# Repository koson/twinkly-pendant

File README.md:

twinkly-pendant
===============

Twinkly pendant or earring, about 25mm diameter PCB with MSP430G2231 14TSSOP, 8x 0805 LEDs, and LiR2032.

The intention is to use near-visible UV LEDs (~395nm). Central area for mounting uranium glass button.

To protect against accidental discharge, unclip from metal chain and/or findings when not in use and 
store in ESD safe packaging.

Versions
--------

_PE01_

Initial prototype with SMD LEDs.

_PE02_

Second prototype with through-hole LEDs.
Buzzer circuit requires 39 mH inductor in parallel with piezo diaphragm.
3 PCBs ordered from OSHpark.

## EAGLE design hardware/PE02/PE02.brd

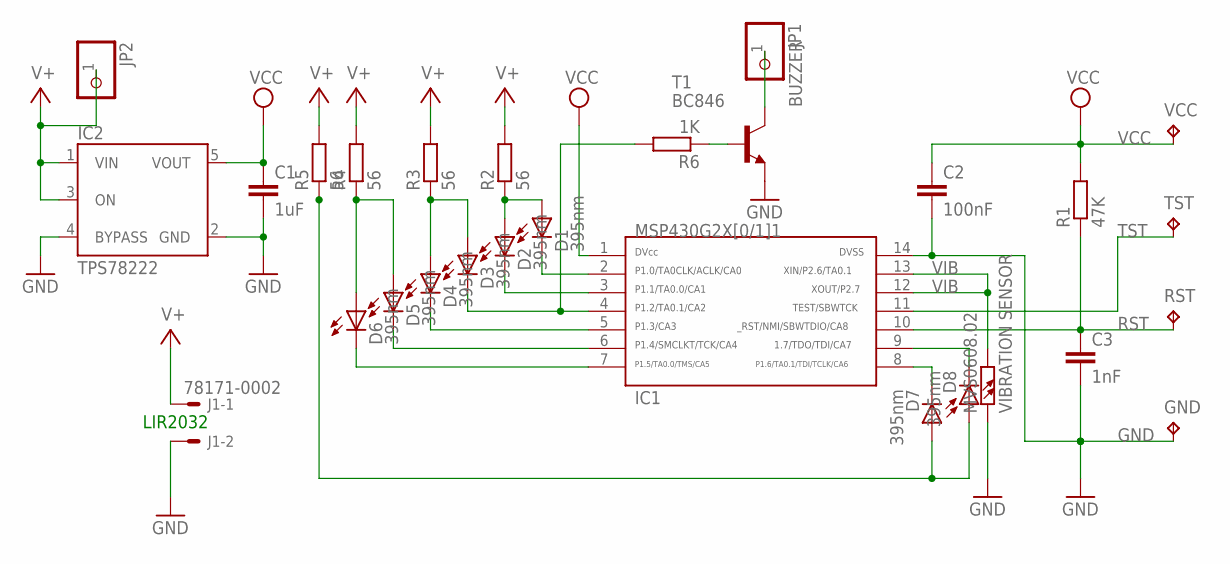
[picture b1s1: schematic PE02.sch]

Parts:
C1: 1uF; 0805
C2: 100nF; 0805
C3: 1nF; 0805
D1, D2, D3, D4, D5, D6, D7, D8: 395nm; LED-3MM
GND: TPTP10R; TP10R
IC1: MSP430G2231; PW14
IC2: TPS78222; SOT23-5
J1: 78171-0002
JP1, JP2: PINHD-1X1CB; 1X01-CLEANBIG
MVS0608.02: VIBRATION SENSOR; R1210
R1: 47K; R0603
R2, R3, R4, R5: 56; R0603
R6: 1K; R0603
RST: TPTP10R; TP10R
T1: BC846; SOT23
TST: TPTP10R; TP10R
VCC: TPTP10R; TP10R

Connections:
BUZZER: JP1.1, T1.3 (C)
GND: C1.2, C2.2, C3.2, GND.TP, IC1.14, IC2.2 (GND), IC2.4 (BYPASS), J1.2, MVS0608.02.1, T1.2 (E)
unnamed: D6.K (C), IC1.7
unnamed: D5.K (C), IC1.6
unnamed: D8.K (C), IC1.9
unnamed: D7.K (C), IC1.8
unnamed: D4.K (C), IC1.5
unnamed: D3.K (C), IC1.4, R6.2
unnamed: D1.K (C), IC1.2
unnamed: R6.1, T1.1 (B)
unnamed: D7.A, D8.A, R5.1
unnamed: D2.K (C), IC1.3
unnamed: D3.A, D4.A, R3.1
unnamed: D5.A, D6.A, R4.1
unnamed: D1.A, D2.A, R2.1
RST: C3.1, IC1.10, R1.1, RST.TP
TST: IC1.11, TST.TP
V+: IC2.1 (VIN), IC2.3 (ON), J1.1, JP2.1, R2.2, R3.2, R4.2, R5.2
VCC: C1.1, C2.1, IC1.1, IC2.5 (VOUT), R1.2, VCC.TP
VIB: IC1.12, IC1.13, MVS0608.02.2

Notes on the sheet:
LIR2032

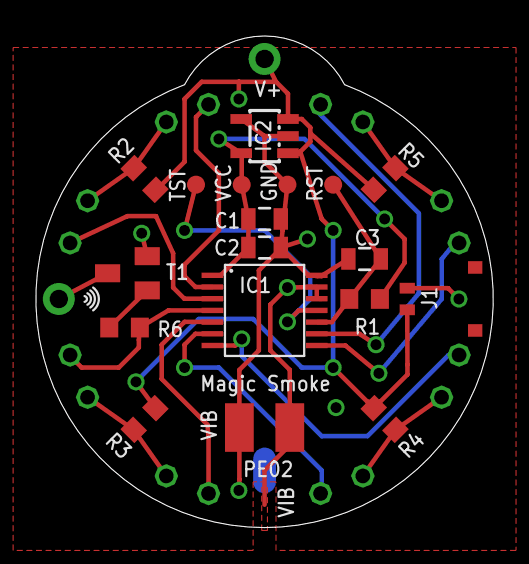
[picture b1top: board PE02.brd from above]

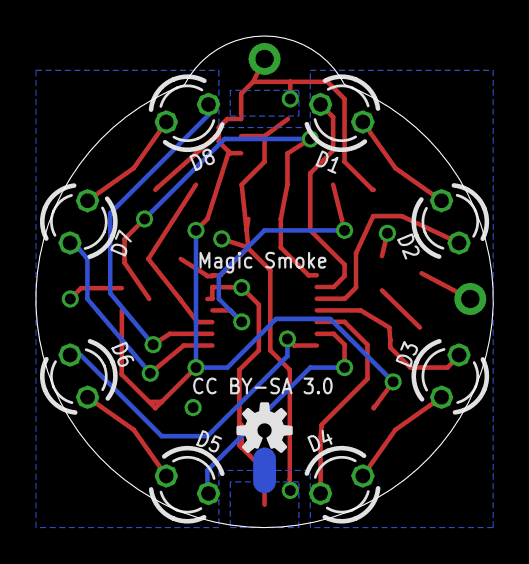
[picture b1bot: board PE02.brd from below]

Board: 2 copper layers, 25.4 x 27.3 mm, 29 parts (9 on the bottom side), 20 nets.

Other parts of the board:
U$1: OSHW-LOGO-S

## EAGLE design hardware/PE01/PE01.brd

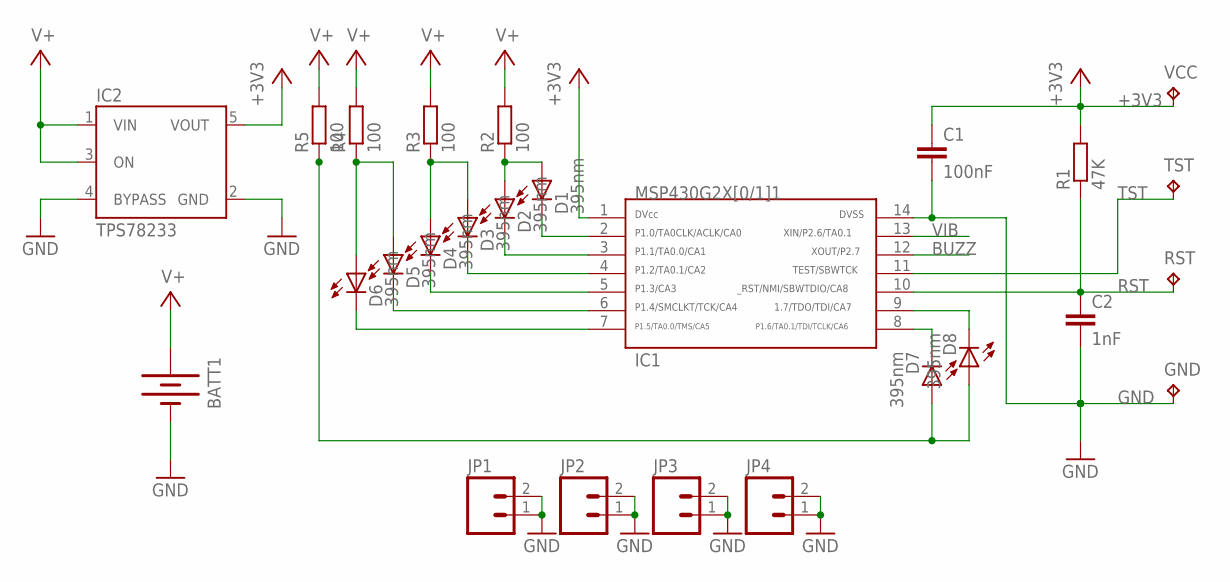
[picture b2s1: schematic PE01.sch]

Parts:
BATT1: BATTERY20MM_4LEGS; BATTCON_20MM_4LEGS
C1: 100nF; 0805
C2: 1nF; 0805
D1, D2, D3, D4, D5, D6, D7, D8: 395nm; LED-805
GND: TPTP10R; TP10R
IC1: MSP430G2231; PW14
IC2: TPS78233; SOT23-5
JP1, JP2, JP3, JP4: M021X02_NO_SILK; 1X02_NO_SILK
R1: 47K; R0603
R2, R3, R4, R5: 100; R0603
RST: TPTP10R; TP10R
TST: TPTP10R; TP10R
VCC: TPTP10R; TP10R

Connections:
+3V3: C1.1, IC1.1, IC2.5 (VOUT), R1.2, VCC.TP
BUZZ: IC1.12
GND: BATT1.2 (-), C1.2, C2.2, GND.TP, IC1.14, IC2.2 (GND), IC2.4 (BYPASS), JP1.1, JP1.2, JP2.1, JP2.2, JP3.1, JP3.2, JP4.1, JP4.2
unnamed: D6.C, IC1.7
unnamed: D5.C, IC1.6
unnamed: D8.C, IC1.9
unnamed: D7.C, IC1.8
unnamed: D4.C, IC1.5
unnamed: D3.C, IC1.4
unnamed: D2.C, IC1.3
unnamed: D1.C, IC1.2
unnamed: D7.A, D8.A, R5.1
unnamed: D3.A, D4.A, R3.1
unnamed: D5.A, D6.A, R4.1
unnamed: D1.A, D2.A, R2.1
RST: C2.1, IC1.10, R1.1, RST.TP
TST: IC1.11, TST.TP
V+: BATT1.1 (+), IC2.1 (VIN), IC2.3 (ON), R2.2, R3.2, R4.2, R5.2
VIB: IC1.13

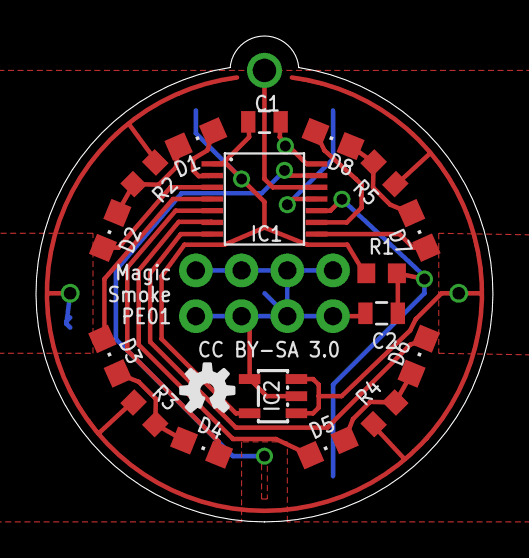
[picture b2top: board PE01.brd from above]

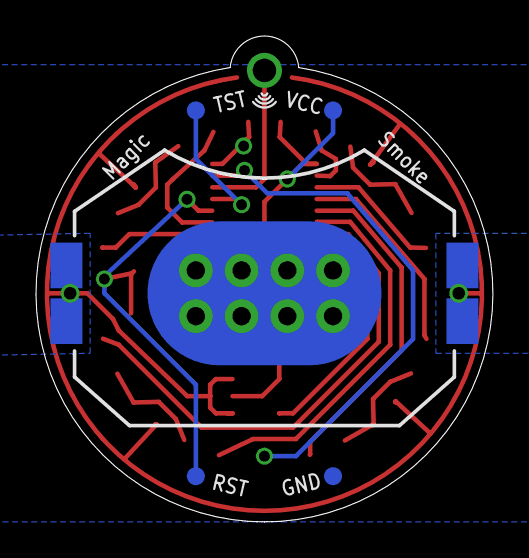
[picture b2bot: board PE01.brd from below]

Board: 2 copper layers, 25.4 x 27.0 mm, 27 parts (5 on the bottom side), 17 nets.

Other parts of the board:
U$1: OSHW-LOGO-S

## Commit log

2014-01-10 PE01 first draft
2014-01-10 Fixed GND, removed slot
2014-01-11 through hole version PE02, 1st draft. LiR with solder tabs. Still need to fix buzzer, vibration sensor.
2014-01-11 Fixed buzzer, need to alter package of GND sewtab to make pad for vibration sensor
2014-01-12 2.2V supply, pullup vibration sensor to output pin
2014-01-12 moved buzzer output to P1.2
2014-01-13 Added Molex Pico-EZmate connector, removed bottom sewtab
2014-01-13 TI manuals
2014-01-13 Very rough prototyping of LED interrupt timing calculations
2014-01-14 fixed stop mask on battery tab pads
2014-01-14 removed sewtab, buzzer hole
2014-01-15 Added piezo buzzer circuit
2014-01-21 Initial draft of firmware. Software PWM working. Rudimentary demo LED patterns. Vibration sensor actions no coded, no debounce on vibration sensor, no turn off.
2014-01-21 PE02 order from OSHpark
2014-01-30 PE02 order from OSHpark, .png files

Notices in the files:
hardware/PE01/PE01.brd:
CC BY-SA 3.0
parts and their libraries:
SparkFun: Licensing: CC v3.0 Share-Alike You are welcome to use this library for commercial purposes.
